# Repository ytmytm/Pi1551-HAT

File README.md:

# PI1551 HAT

A minimalistic HAT for Raspberry Pi 3A/3B/3B+ that gives you low-cost **1551 floppy emulation** (and optionally **TAP tape playback**) for Commodore C16/C116 or Plus/4. You build only what you need: the core is a few parts; display, controls, and TAP support are optional add-ons.

**Warning: For [tcbm2sd](https://github.com/ytmytm/plus4-tcbm2sd) ONLY. Do not connect this HAT to a real 1551 drive. The circuit is not 5V-tolerant and can damage the Raspberry Pi.**

---

## What to build (at a glance)

This is a HAT board that sits on top of a Raspberry Pi. You need to have a Raspberry Pi 3A or 3B and a capable (at least 2A) USB-Micro power supplier for it.

| Goal | You need |
|------|----------|
| **1551 emulation only** | PCB + required parts below + 16-wire ribbon cable + [tcbm2sd](https://github.com/ytmytm/plus4-tcbm2sd). No display, no buttons (disk commands only or HDMI+USB keyboard). |
| **1551 + menu on device** | Above + **one of**: 5 buttons, or 2 buttons + rotary encoder (ALPS EC11E or KY-040). Optionally add OLED and/or LED. |
| **1551 + TAP playback** | Above + TAP_READ block (Q2, R5, R8) + MiniDIN-7 socket or J5 header + cable to computer. Rest of TAP circuit is optional but recommended (see [TAP playback](#tap-playback)). |

Everything not in the “required parts” list is optional. You can add options later.

---

## Origin

Cloned from [PI1541 Hat](https://github.com/tebl/C64-Pi1541-module), adapted for 1551 and tape playback.

## Software

Firmware: [Pi1551](https://github.com/ytmytm/Pi1551) (branch `pi1551`).

## Hardware

The [Releases](https://github.com/ytmytm/Pi1551-HAT/releases) section contains all the files you need for manufacturing the PCB with SMD parts populated. That includes Gerber files, BOM with JLCPCB part numbers and SMD part positions.

- [Schematic PDF](plots/RPi_Hat.pdf)
- [Gerbers](plots/)

### Required parts (1551 emulation)

- 40×2 female header for Raspberry Pi GPIO
- 2×8 (16-pin) male IDC connector for ribbon cable to [tcbm2sd](https://github.com/ytmytm/plus4-tcbm2sd)
- D2: Schottky diode (BAT54, BAS40, BAT43 or 1N5819) — protects the Pi
- R2: 10K resistor (with D2)
- R11-23: 13×10K resistors (TCBM pullups)

Plus a **straight 16-wire ribbon cable**. Connections are 1:1; both ends must be crimped the same way. I recommend crimping the cable the same way as in the photo above, with both connectors identical — it makes cable routing easier on both ends.

You can order the PCB with SMD parts pre-populated:

### Optional: display

- OLED: SSD1306 128×64 or 128×32, or SH1106 128×64 (SH1106 is large - there is no room for rotary encoder, use 5 buttons instead).
- Pinout selectable by solder jumpers: GND/VCC/SCL/SCL (default) or VCC/GND/SCL/SCL.

### Optional: drive LED

- 3 mm or 5 mm LED + R1 (e.g. 220 Ω).

### Optional: audio

- 3 V buzzer with built-in oscillator.

### Optional: controls (pick one set)

- **Option A:** 5× 6×6 mm tact switches (SW1–SW5).
- **Option B:** 2× 6×6 mm tact switches (SW4-SW5) + rotary encoder (ALPS EC11E or a KY-040 module).

### TAP playback

To play TAP files you need:

- **TAP_READ block:** Q2, R5, R8 (required for tape in).
- **Connector:** MiniDIN-7 socket (J4) **or** 1×7 pin header (J5) to solder the cable.
- **Cable:** At least TAP_READ and GND; one end must be Mini-DIN-7 male.

A MiniDin-7 cable from Aliexpress may not fit Plus/4 cassette port because the squared plug won't fit the round hole in Plus/4 case. Just shave off the corners to make it more round. It may not look pretty, but it will work. 

If you intend to solder the cable yourself, the order of signals on J5 is such that it's easy to solder a piece of ribbon cable to a Mini-DIN-7 plug by going around the perimeter (see schematic for both pinouts). 

The rest of the TAP circuit is optional, but recommended:

- **TAP_SENSE** (Q1, R3, R4): lets the computer see “tape PLAY pressed”. If you omit it, close jumper JP1 so SENSE is always active.
- **MOTOR** (Q4, R7, R10): lets the computer control motor line. If you omit it, close JP2 so motor is always enabled (fine for Pi1551).

You can also leave all parts in and configure behaviour in the [Pi1551](https://github.com/ytmytm/Pi1551) config.

*If your Plus/4 has a 6510 CPU swap, it cannot drive the MOTOR line (see [this note](https://hackjunk.com/2017/06/23/commodore-16-plus-4-8501-to-6510-cpu-conversion/)). You can still have MOTOR active all the time via the [Pi1551](https://github.com/ytmytm/Pi1551) configuration file.*

**TAP_WRITE** (Q3, R6, R9) is on the PCB for future use when Pi1551 supports tape write.

## PCB

The board is a mixture of THT and SMD parts.

Don't be afraid of SMD parts, I have used larger footprints that are more friendly for hand soldering. You need tweezers, a steady hand, iron with a fine tip and a 0.5mm solder. Use the flux generously.

Note the D2 diode orientation - the stripe is on the same side as the closed silkscreen, towards the TCBM connector. 

For convenience, the majority of resistors (R2-R23) are all the same. Use any value in the 1K-10K range you have at hand.

You might find that soldering those four SMD transistors, ten resistors and one diode is faster than their THT counterparts.

## BOM

Count of optional parts in brackets.

| Reference | Item                                   | Count |
| --------- | -------------------------------------- | ----- |
| J1        | 2x20 pin long female header            |     1 |
| J2        | 2x8 pin IDC 16P socket                 |     1 |
| J3        | KY-040 rotary encoder module           |    (1)|
| J4        | MiniDIN-7 female socket                |    (1)|
| J5        | 1x7 pin long male header               |    (1)|
| BZ1       | Buzzer (5mm / 7mm pin spacing), 3V     |    (1)|
| IC1       | SSD1306 OLED-display 128x64 (0.96")    |    (1)|
| IC2       | SSD1306 OLED-display 128x32 (0.91")    |    (1)|
| SW1-SW5   | Momentary push button, 6x6mm           |    (5)|
| SW6       | ALPS EC11E rotary encoder or similar   |    (1)|
| D1        | 3mm / 5mm LED (e.g. red for authenticity)               |    (1)|
| D2        | Schottky diode: BAT54, 1n5819, BAT43, etc. |    1 |
| R1        | 100-220 Ohm (for LED)                  |    (1)|
| R2-R23    | 1K-10K Ohm (R2 required; rest optional)|  14+(8)|
| Q1-Q4     | MMBT3904 / 2N3904 transistors          |    (4) |

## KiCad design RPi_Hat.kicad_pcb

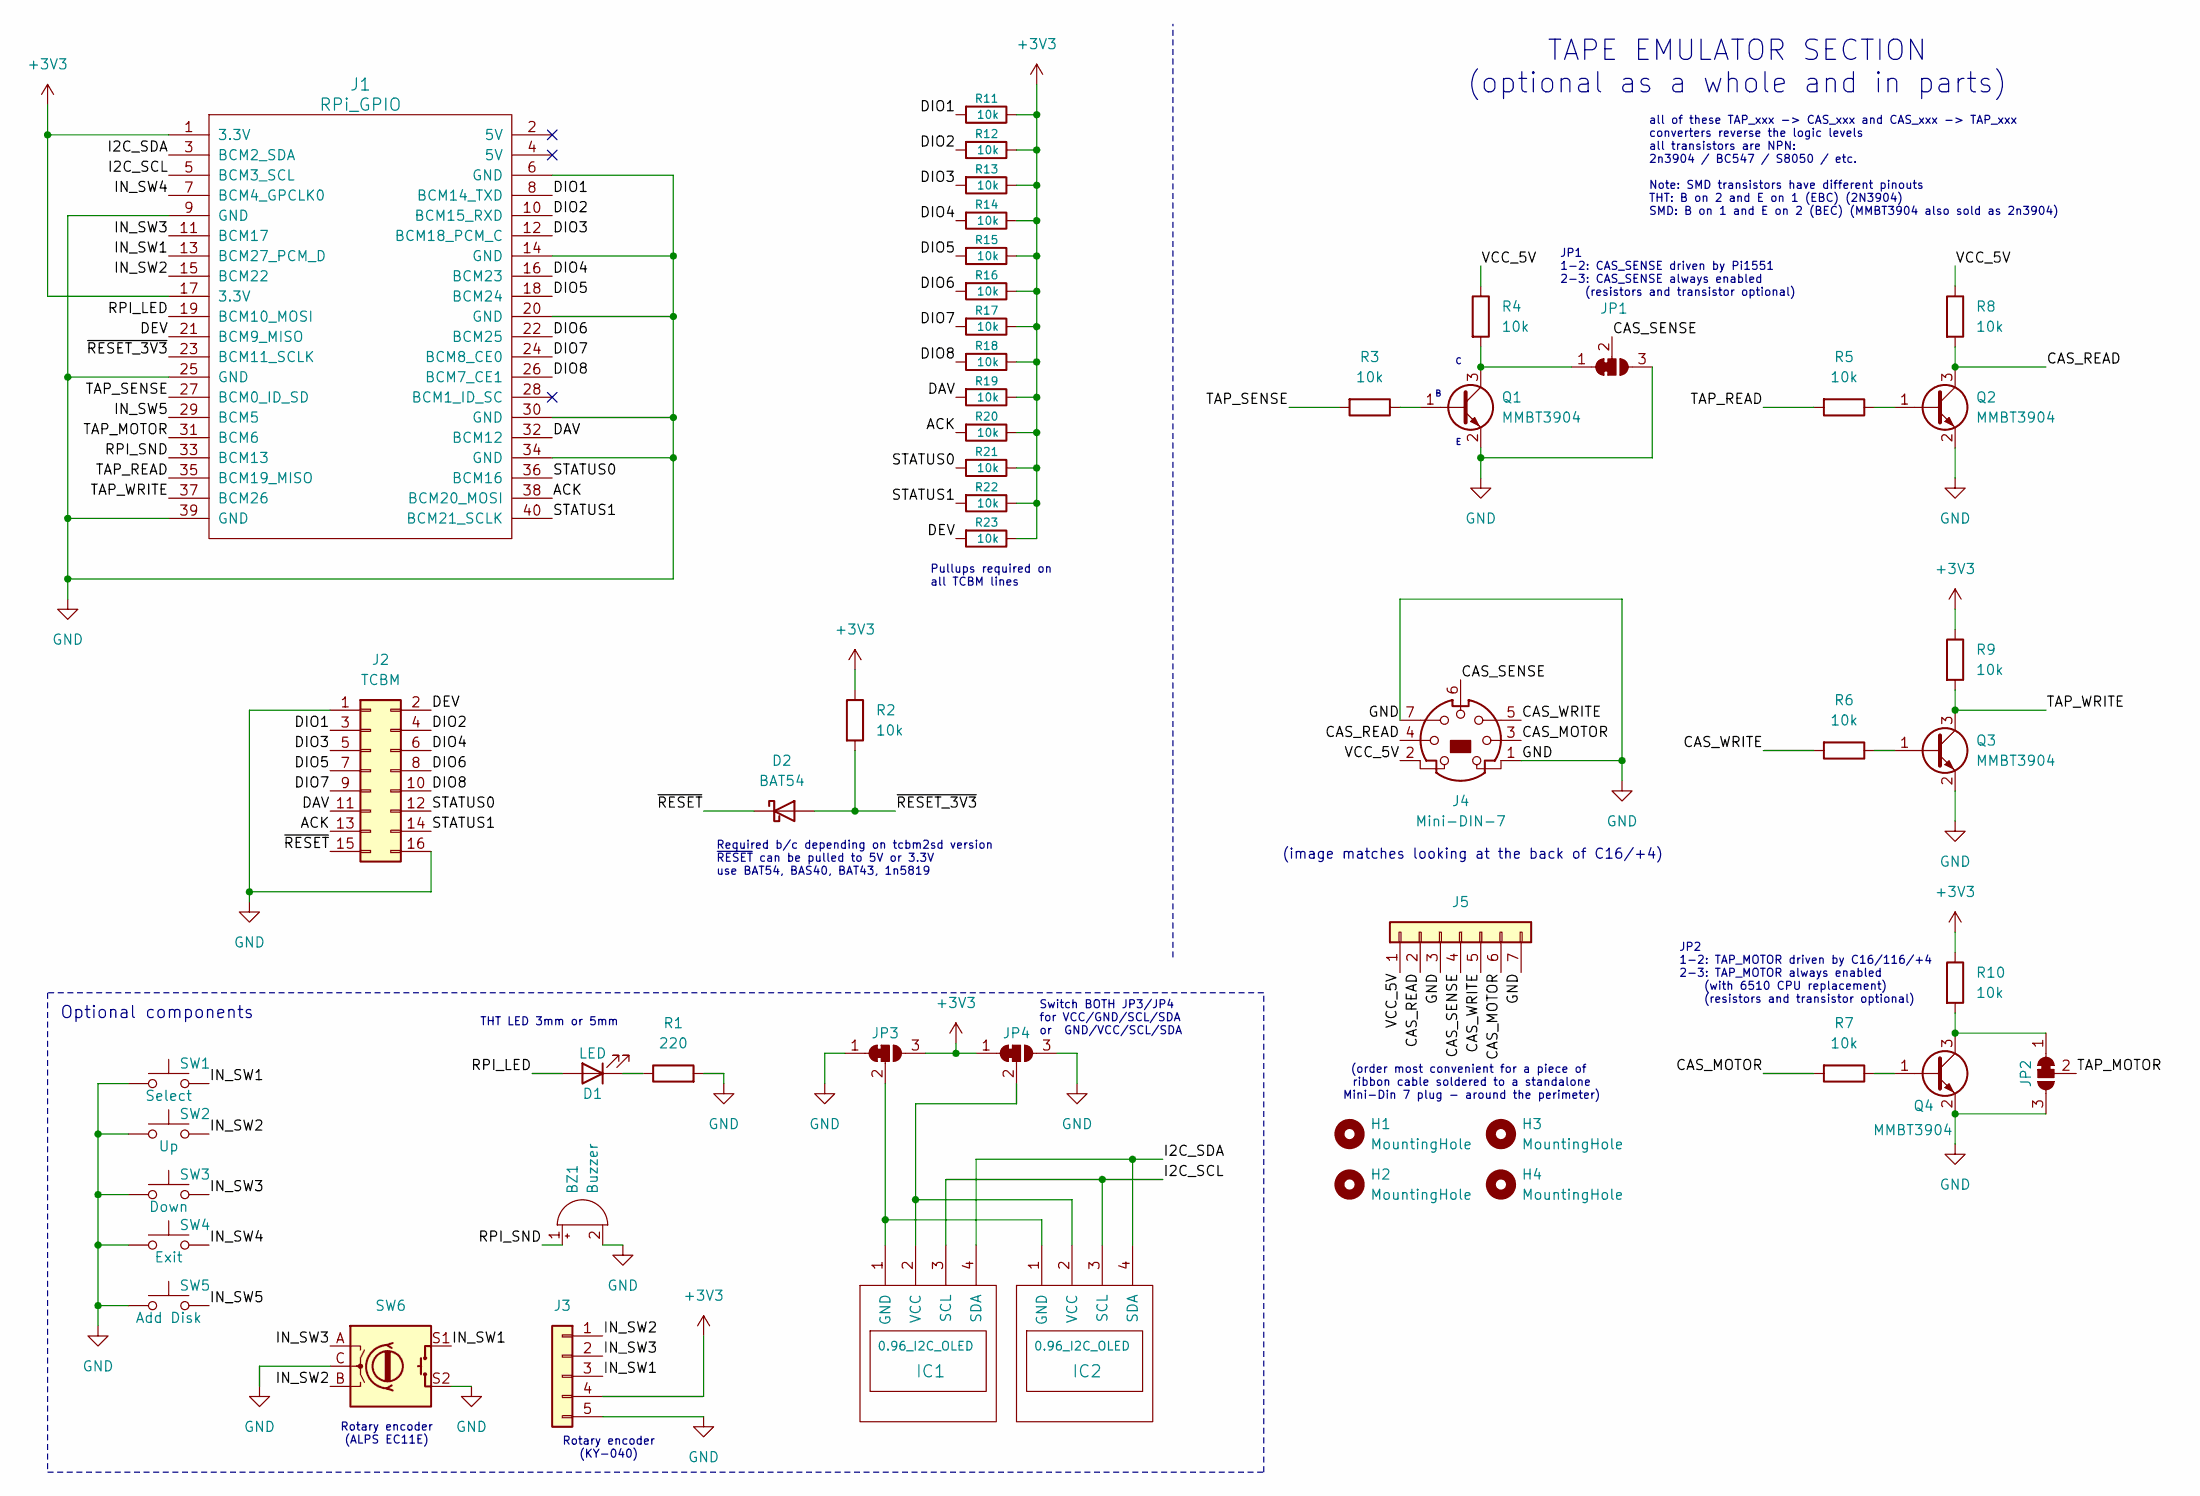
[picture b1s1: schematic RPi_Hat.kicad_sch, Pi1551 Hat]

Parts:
BZ1: Buzzer; Buzzer_12x9.5RM7.6
D1: LED; LED_D3.0mm
D2: BAT54; D_SOD-123; MFR.Part # BAT54W; JLCPCB Part # C7502705
H1, H2, H3, H4: MountingHole; MountingHole_2.7mm_M2.5_DIN965
IC1: 0.96_I2C_OLED; 0.91_I2C_OLED
IC2: 0.96_I2C_OLED
J1: RPi_GPIO; PinHeader_2x20_P2.54mm_Vertical
J2: TCBM; IDC-Header_2x08_P2.54mm_Vertical
J3: Conn_01x05; PinHeader_1x05_P2.54mm_Vertical
J4: Mini-DIN-7; Mini_DIN_round_7_canned
J5: Conn_01x07; PinHeader_1x07_P2.54mm_Horizontal
JP1, JP2, JP3, JP4: SolderJumper_3_Bridged12; SolderJumper-3_P1.3mm_Bridged12_RoundedPad1.0x1.5mm_NumberL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
Q1, Q2, Q3, Q4: MMBT3904; SOT-23_Handsoldering; MFR.Part # 2N3904S-RTK/PS; JLCPCB Part # C18536
R1: 220; R_0805_2012Metric_Pad1.20x1.40mm_HandSolder; MFR.Part # 0805W8F2200T5E; JLCPCB Part # C17557
R2, R3, R4, R5, R6, R7, R8, R9, R10, R11, R12, R13, R14, R15, R16, R17, R18, R19, R20, R21, R22, R23: 10k; R_0805_2012Metric_Pad1.20x1.40mm_HandSolder; MFR.Part # RCA0510KFLF; JLCPCB Part # C22356686
SW1: Select; SW_PUSH_6mm_H5mm
SW2: Up; SW_PUSH_6mm_H5mm
SW3: Down; SW_PUSH_6mm_H5mm
SW4: Exit; SW_PUSH_6mm_H5mm
SW5: Add Disk; SW_PUSH_6mm_H5mm
SW6: RotaryEncoder_Switch; RotaryEncoder_Alps_EC11E-Switch_Vertical_H20mm_CircularMoun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; MFR.Part # EC11E15244B2; JLCPCB Part # C470754

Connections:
+3V3: J1.1 (3.3V), J1.17 (3.3V), J3.4, JP3.3 (B), JP4.1 (A), R2.1, R9.1, R10.1, R11.1, R12.1, R13.1, R14.1, R15.1, R16.1, R17.1, R18.1, R19.1, R20.1, R21.1, R22.1, R23.1
/ACK: J1.38 (BCM20_MOSI), J2.13, R20.2
/CAS_MOTOR: J4.3, J5.6, R7.2
/CAS_READ: J4.4, J5.2, Q2.3 (C), R8.2
/CAS_SENSE: J4.6, J5.4, JP1.2 (C)
/CAS_WRITE: J4.5, J5.5, R6.2
/DAV: J1.32 (BCM12), J2.11, R19.2
/DEV: J1.21 (BCM9_MISO), J2.2, R23.2
/DIO1: J1.8 (BCM14_TXD), J2.3, R11.2
/DIO2: J1.10 (BCM15_RXD), J2.4, R12.2
/DIO3: J1.12 (BCM18_PCM_C), J2.5, R13.2
/DIO4: J1.16 (BCM23), J2.6, R14.2
/DIO5: J1.18 (BCM24), J2.7, R15.2
/DIO6: J1.22 (BCM25), J2.8, R16.2
/DIO7: J1.24 (BCM8_CE0), J2.9, R17.2
/DIO8: J1.26 (BCM7_CE1), J2.10, R18.2
/I2C_SCL: IC1.3 (SCL), IC2.3 (SCL), J1.5 (BCM3_SCL)
/I2C_SDA: IC1.4 (SDA), IC2.4 (SDA), J1.3 (BCM2_SDA)
/IN_SW1: J1.13 (BCM27_PCM_D), J3.3, SW1.2, SW6.S1
/IN_SW2: J1.15 (BCM22), J3.1, SW2.2, SW6.B
/IN_SW3: J1.11 (BCM17), J3.2, SW3.2, SW6.A
/IN_SW4: J1.7 (BCM4_GPCLK0), SW4.2
/IN_SW5: J1.29 (BCM5), SW5.2
/RPI_LED: D1.2 (A), J1.19 (BCM10_MOSI)
/RPI_SND: BZ1.1 (+), J1.33 (BCM13)
/STATUS0: J1.36 (BCM16), J2.12, R21.2
/STATUS1: J1.40 (BCM21_SCLK), J2.14, R22.2
/TAP_MOTOR: J1.31 (BCM6), JP2.2 (C)
/TAP_READ: J1.35 (BCM19_MISO), R5.2
/TAP_SENSE: J1.27 (BCM0_ID_SD), R3.2
/TAP_WRITE: J1.37 (BCM26), Q3.3 (C), R9.2
/VCC_5V: J4.2, J5.1, R4.1, R8.1
/~RESET_3V3: D2.2 (A), J1.23 (BCM11_SCLK), R2.2
/~RESET: D2.1 (K), J2.15
GND: BZ1.2 (-), J1.6 (GND), J1.9 (GND), J1.14 (GND), J1.20 (GND), J1.25 (GND), J1.30 (GND), J1.34 (GND), J1.39 (GND), J2.1, J2.16, J3.5, J4.1, J4.7, J5.3, J5.7, JP1.3 (B), JP2.3 (B), JP3.1 (A), JP4.3 (B), Q1.2 (E), Q2.2 (E), Q3.2 (E), Q4.2 (E), R1.2, SW1.1, SW2.1, SW3.1, SW4.1, SW5.1, SW6.C, SW6.S2
unnamed: D1.1 (K), R1.1
unnamed: IC1.1 (GND), IC2.1 (GND), JP3.2 (C)
unnamed: IC1.2 (VCC), IC2.2 (VCC), JP4.2 (C)
unnamed: JP1.1 (A), Q1.3 (C), R4.2
unnamed: JP2.1 (A), Q4.3 (C), R10.2
unnamed: Q1.1 (B), R3.1
unnamed: Q2.1 (B), R5.1
unnamed: Q3.1 (B), R6.1
unnamed: Q4.1 (B), R7.1

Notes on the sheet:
all of these TAP_xxx -> CAS_xxx and CAS_xxx -> TAP_xxx converters reverse the logic levels all transistors are NPN: 2n3904 / BC547 / S8050 / etc. Note: SMD transistors have different pinouts THT: B on 2 and E on 1 (EBC) (2N3904) SMD: B on 1 and E on 2 (BEC) (MMBT3904 also sold as 2n3904)
Optional components
JP2 1-2: TAP_MOTOR driven by C16/116/+4 2-3: TAP_MOTOR always enabled (with 6510 CPU replacement) (resistors and transistor optional)
TAPE EMULATOR SECTION (optional as a whole and in parts)
Rotary encoder (KY-040)
Rotary encoder (ALPS EC11E)
Pullups required on all TCBM lines
JP1 1-2: CAS_SENSE driven by Pi1551 2-3: CAS_SENSE always enabled (resistors and transistor optional)
THT LED 3mm or 5mm
(image matches looking at the back of C16/+4)
(order most convenient for a piece of ribbon cable soldered to a standalone Mini-Din 7 plug - around the perimeter)
Switch BOTH JP3/JP4 for VCC/GND/SCL/SDA or GND/VCC/SCL/SDA
Required b/c depending on tcbm2sd version ~{RESET} can be pulled to 5V or 3.3V use BAT54, BAS40, BAT43, 1n5819

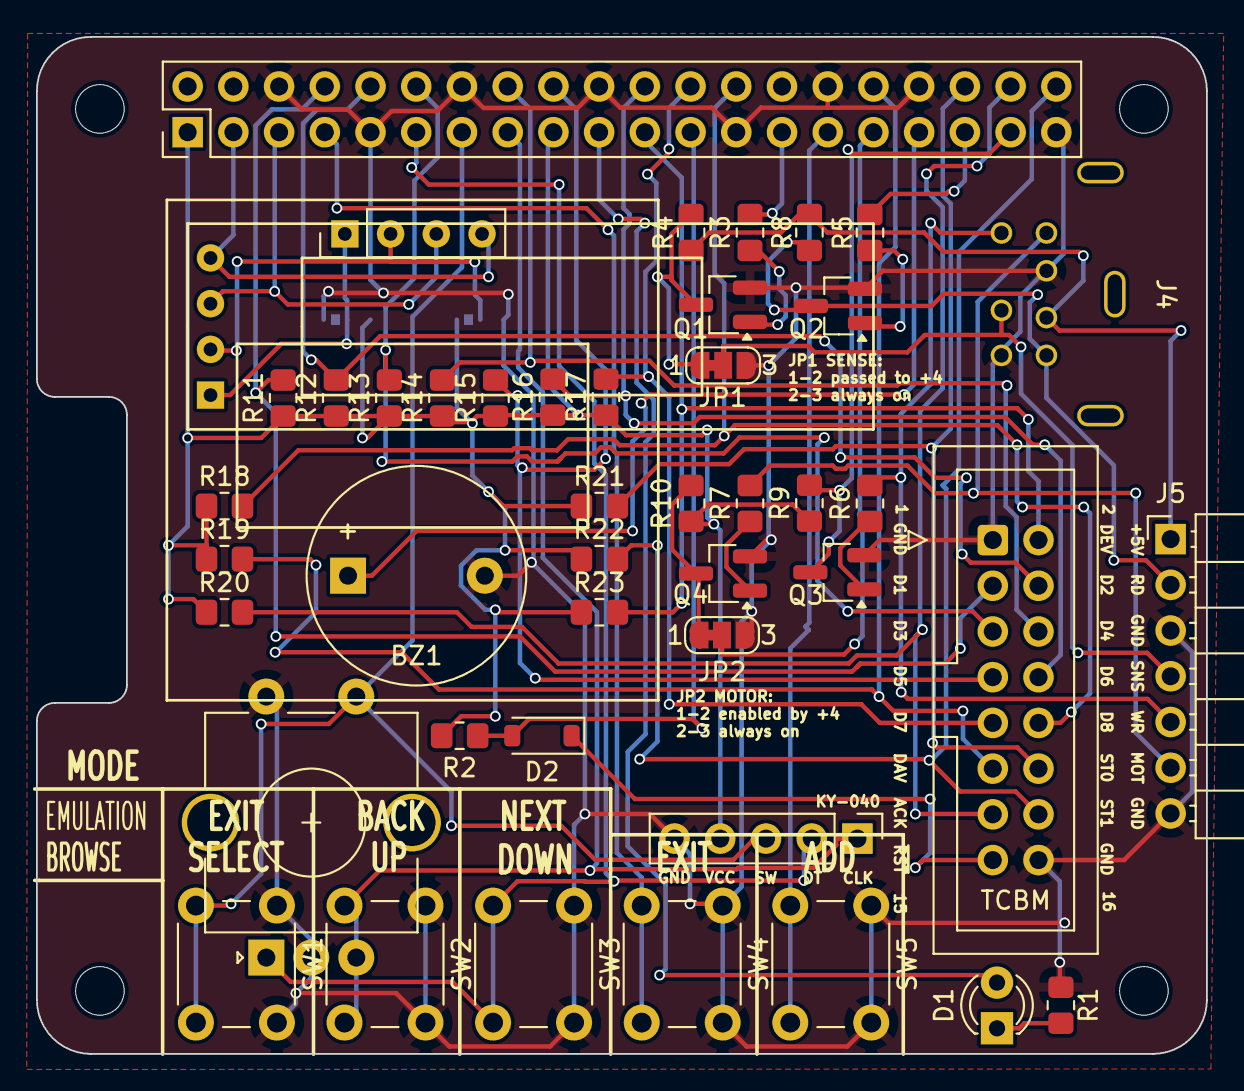
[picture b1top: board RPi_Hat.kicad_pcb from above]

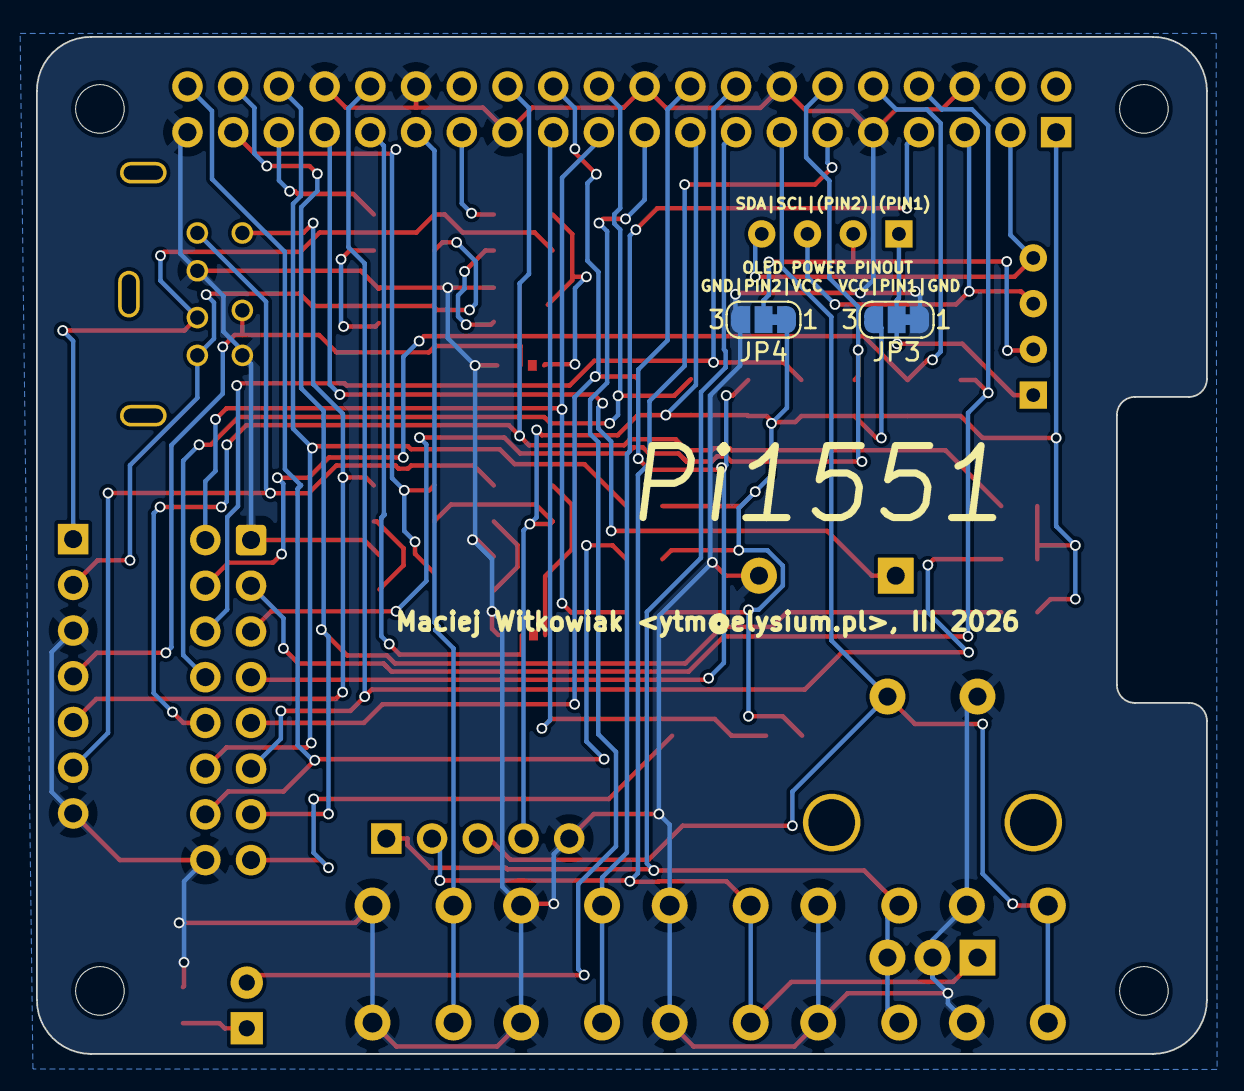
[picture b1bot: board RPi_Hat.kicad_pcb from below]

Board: 2 copper layers, 65.0 x 56.5 mm, 51 parts (2 on the bottom side), 44 nets.

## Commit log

2025-11-16 pi1551 hat, test version (20251022)
2025-11-16 remove unused libs
2025-11-16 exclusion zones and group TCBM connector silkscreen
2025-12-07 /RESET voltage level protection, connector for rotary encoder, tape connector support
2025-12-14 completed tht version with tape interface support
2025-12-14 Conn_DIN_round parts from https://forum.kicad.info/t/mini-din-connectors-their-footprints-and-3-d-models-asking-for-discussion-and-a-bit-of-help-discussion/58247/11
2025-12-28 SMD rework and updates
2025-12-28 completed plots
2025-12-28 final version for test fabrication, added encoder part directly (without module, without pullups)
2026-02-01 - correct part and pinout for SMD 2n3904 transistor - added jumpers to configure VCC/GND routing for OLED screens - moved encoder to the left, module socket to the right
2026-02-01 remove Pi1551 Hat gerbers and media
2026-02-01 docs update pre-release
2026-02-09 gerbers for fabrication
2026-02-27 Update
    Clarified ribbon cable instructions and updated component descriptions.
2026-02-27 Clarify
    Updated the recommendation for crimping the ribbon cable to clarify that both connectors should be done in the same way.
2026-02-28 updated, clarified
2026-03-01 typo
2026-03-01 clarified
2026-03-08 Tape cable hint
2026-03-10 TCBM pullups are required
